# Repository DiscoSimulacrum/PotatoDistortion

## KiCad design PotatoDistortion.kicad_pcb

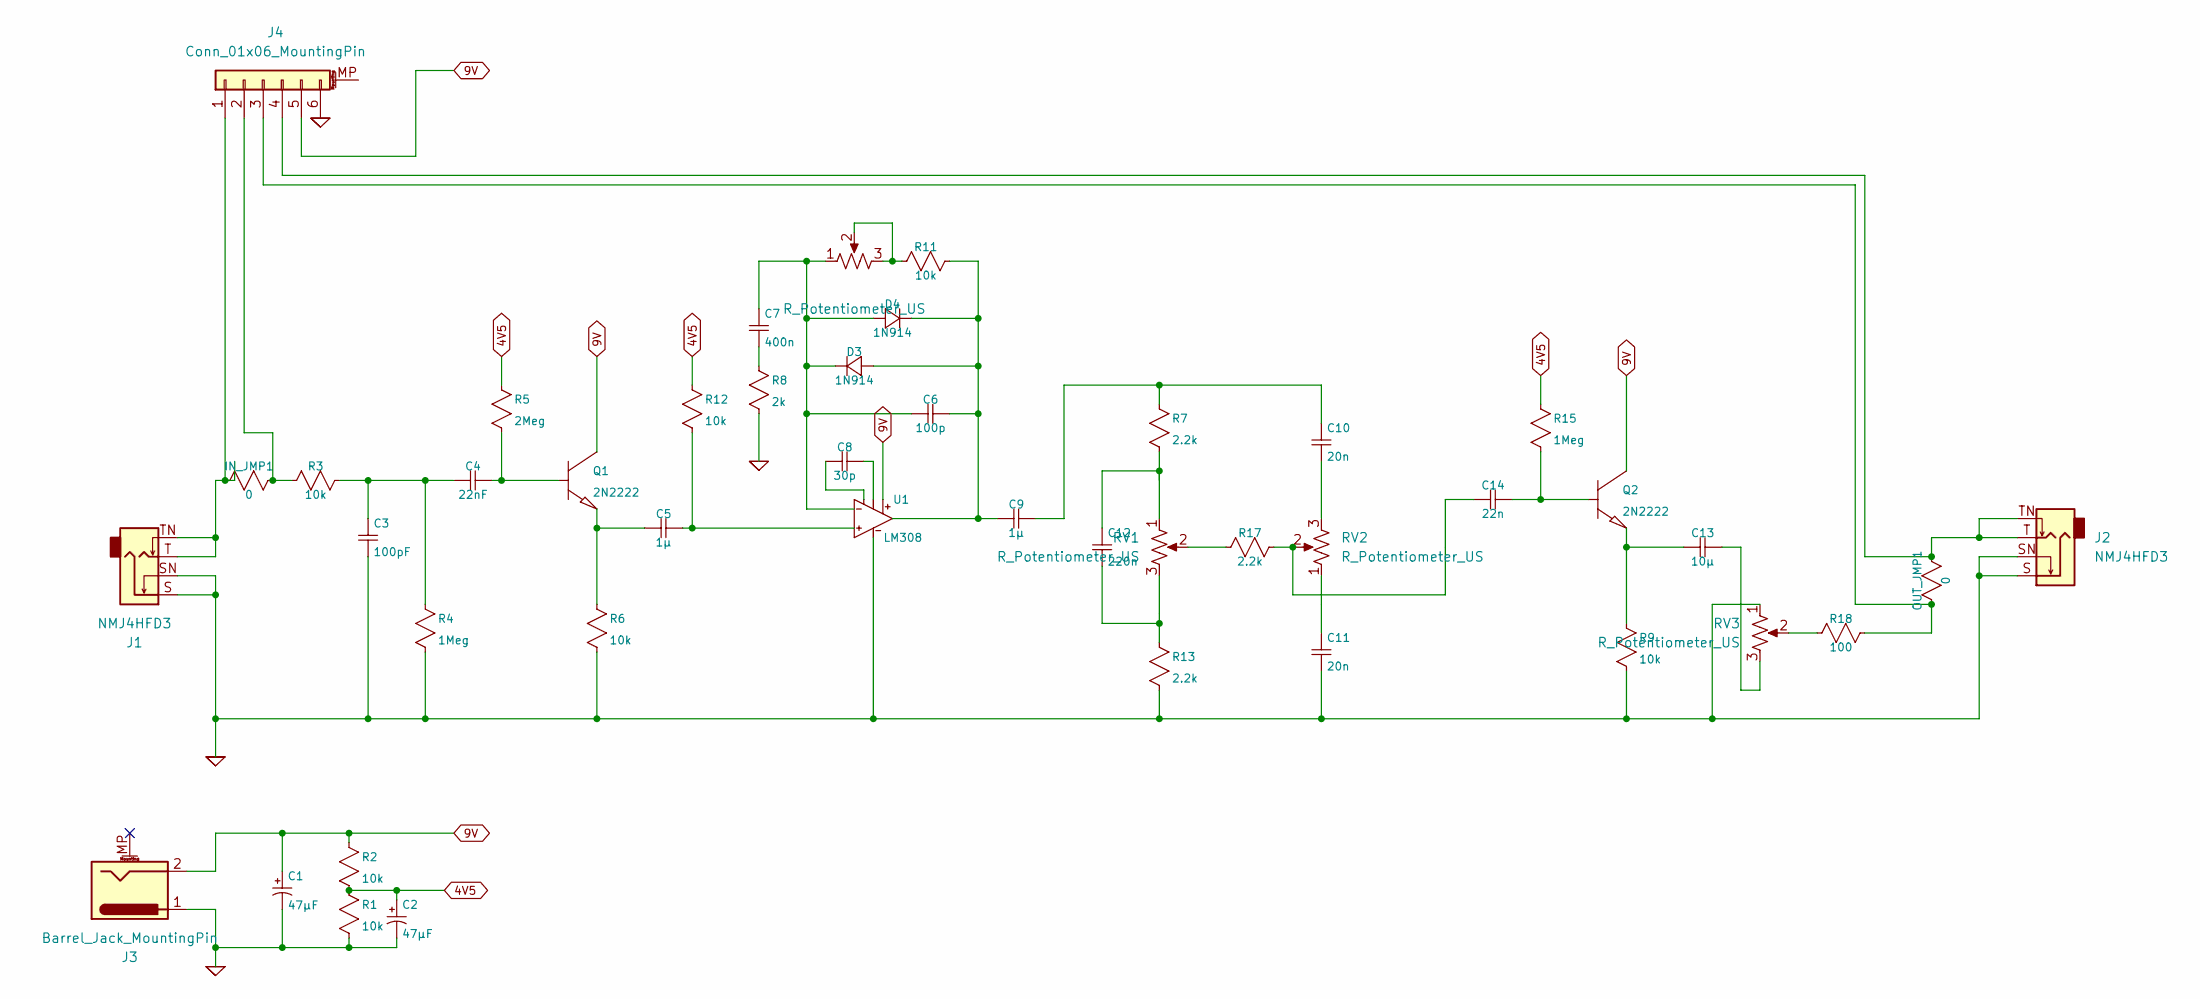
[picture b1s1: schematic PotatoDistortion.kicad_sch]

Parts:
C1, C2: 47µF; CP_Radial_D4.0mm_P2.00mm
C3: 100pF; C_Disc_D4.3mm_W1.9mm_P5.00mm
C4: 22nF; C_Disc_D4.3mm_W1.9mm_P5.00mm
C5, C9: 1µ; C_Disc_D4.3mm_W1.9mm_P5.00mm
C6: 100p; C_Disc_D4.3mm_W1.9mm_P5.00mm
C7: 400n; C_Disc_D4.3mm_W1.9mm_P5.00mm
C8: 30p; C_Disc_D4.3mm_W1.9mm_P5.00mm
C10, C11: 20n; C_Disc_D4.3mm_W1.9mm_P5.00mm
C12: 220n; C_Disc_D4.3mm_W1.9mm_P5.00mm
C13: 10µ; C_Disc_D4.3mm_W1.9mm_P5.00mm
C14: 22n; C_Disc_D4.3mm_W1.9mm_P5.00mm
D3, D4: 1N914; D_DO-201AE_P12.70mm_Horizontal
IN_JMP1: 0; R_Axial_DIN0207_L6.3mm_D2.5mm_P7.62mm_Horizontal
J1, J2: NMJ4HFD3; Jack_6.35mm_Neutrik_NMJ4HFD3_Horizontal
J3: Barrel_Jack_MountingPin; BarrelJack_Horizontal
J4: Conn_01x06_MountingPin; PinSocket_1x06_P2.00mm_Vertical
OUT_JMP1: 0; R_Axial_DIN0207_L6.3mm_D2.5mm_P7.62mm_Horizontal
Q1, Q2: 2N2222; TO-92
R1, R2, R3, R6, R9, R11, R12: 10k; R_Axial_DIN0309_L9.0mm_D3.2mm_P12.70mm_Horizontal
R4, R15: 1Meg; R_Axial_DIN0309_L9.0mm_D3.2mm_P12.70mm_Horizontal
R5: 2Meg; R_Axial_DIN0309_L9.0mm_D3.2mm_P12.70mm_Horizontal
R7, R13, R17: 2.2k; R_Axial_DIN0309_L9.0mm_D3.2mm_P12.70mm_Horizontal
R8: 2k; R_Axial_DIN0309_L9.0mm_D3.2mm_P12.70mm_Horizontal
R18: 100; R_Axial_DIN0309_L9.0mm_D3.2mm_P12.70mm_Horizontal
RV1, RV2, RV3, RV4: R_Potentiometer_US; Potentiometer_Alps_RK09L_Single_Vertical
U1: LM308; DIP-8_W7.62mm_Socket_LongPads

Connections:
0: C1.2 (B), C2.2 (B), C3.2, C11.2, J1.S, J1.SN, J2.S, J2.SN, J3.1, J4.6, R1.2, R4.2, R6.2, R8.2, R9.2, R13.2, RV3.1, U1.4 (V-)
4V5: C2.1 (A), R1.1, R2.2, R5.1, R12.1, R15.1
9V: C1.1 (A), J3.2, J4.5, Q1.1 (C), Q2.1 (C), R2.1, U1.3 (V+)
unnamed: C3.1, C4.2, R3.1, R4.1
unnamed: C7.2, R8.1
unnamed: C9.1, C10.1, R7.1
unnamed: C10.2, RV2.3
unnamed: C11.1, RV2.1
unnamed: C12.1, R7.2, RV1.1
unnamed: C12.2, R13.1, RV1.3
unnamed: C13.1, RV3.3
unnamed: C14.2, R17.1, RV2.2
unnamed: C6.1, C9.2, D3.1 (+), D4.2 (-), R11.1, U1.5 (OUT)
unnamed: C6.2, C7.1, D3.2 (-), D4.1 (+), RV4.1, U1.2 (In-)
unnamed: IN_JMP1.2, J1.T, J1.TN, J4.1
unnamed: IN_JMP1.1, J4.2, R3.2
unnamed: J4.3, OUT_JMP1.2, R18.1
unnamed: J2.T, J2.TN, J4.4, OUT_JMP1.1
unnamed: C4.1, Q1.2 (B), R5.2
unnamed: C5.2, Q1.3 (E), R6.1
unnamed: C14.1, Q2.2 (B), R15.2
unnamed: C13.2, Q2.3 (E), R9.1
unnamed: R11.2, RV4.2, RV4.3
unnamed: R17.2, RV1.2
unnamed: R18.2, RV3.2
unnamed: C8.2, U1.6 (COMP1)
unnamed: C8.1, U1.7 (COMP2)
unnamed: C5.1, R12.2, U1.1 (In+)

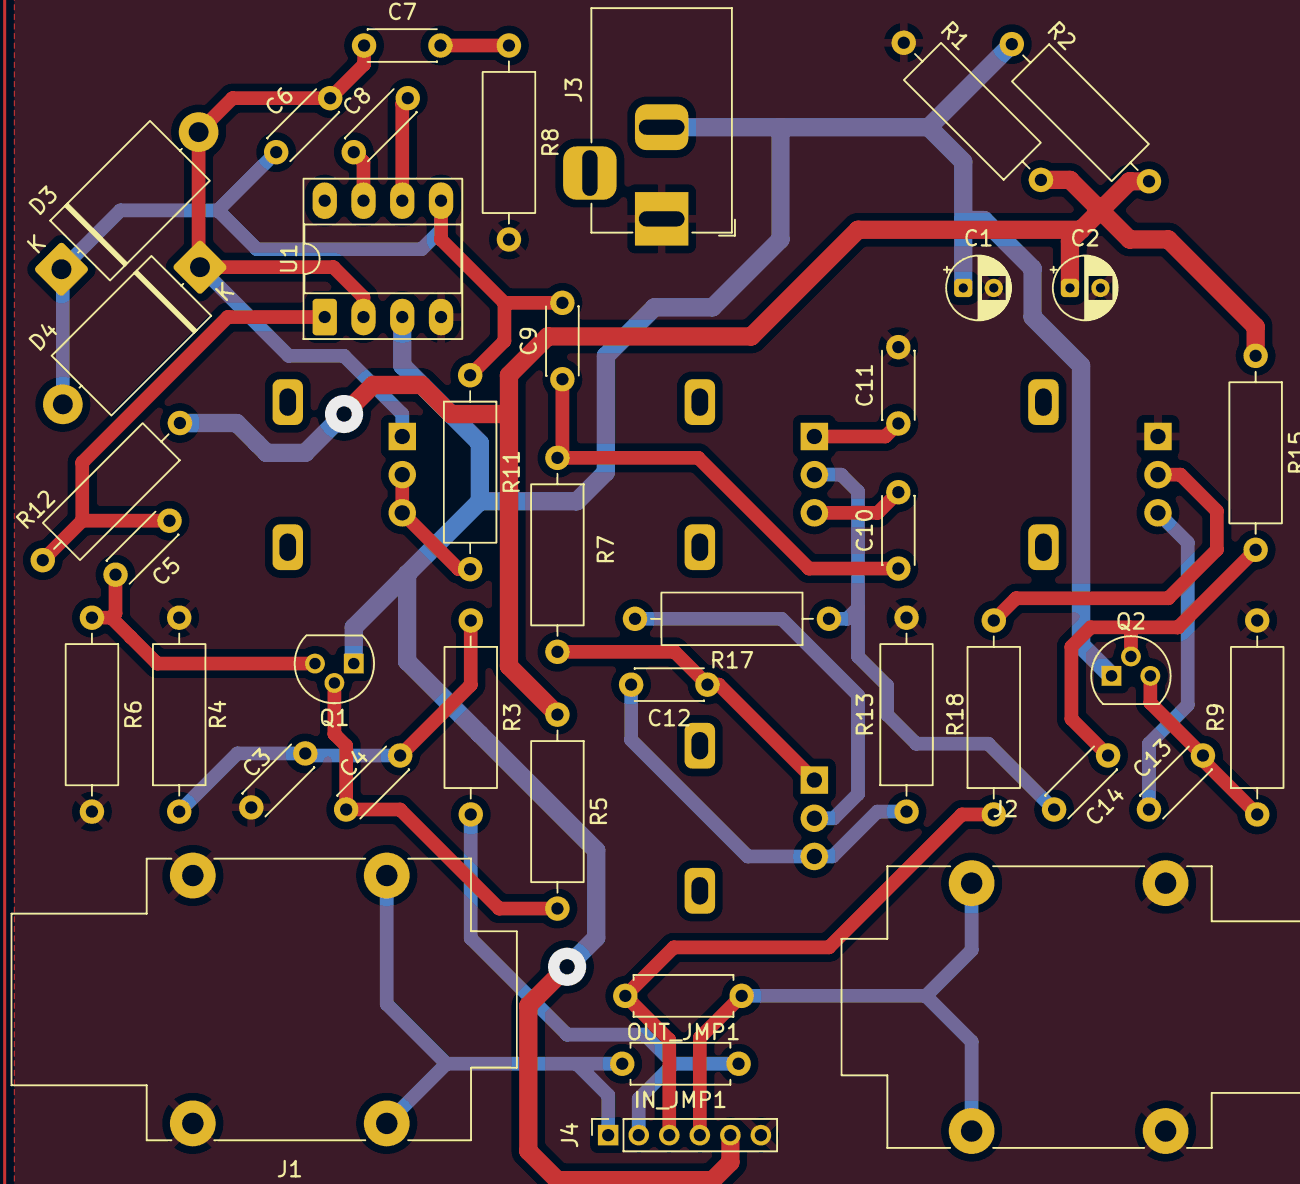
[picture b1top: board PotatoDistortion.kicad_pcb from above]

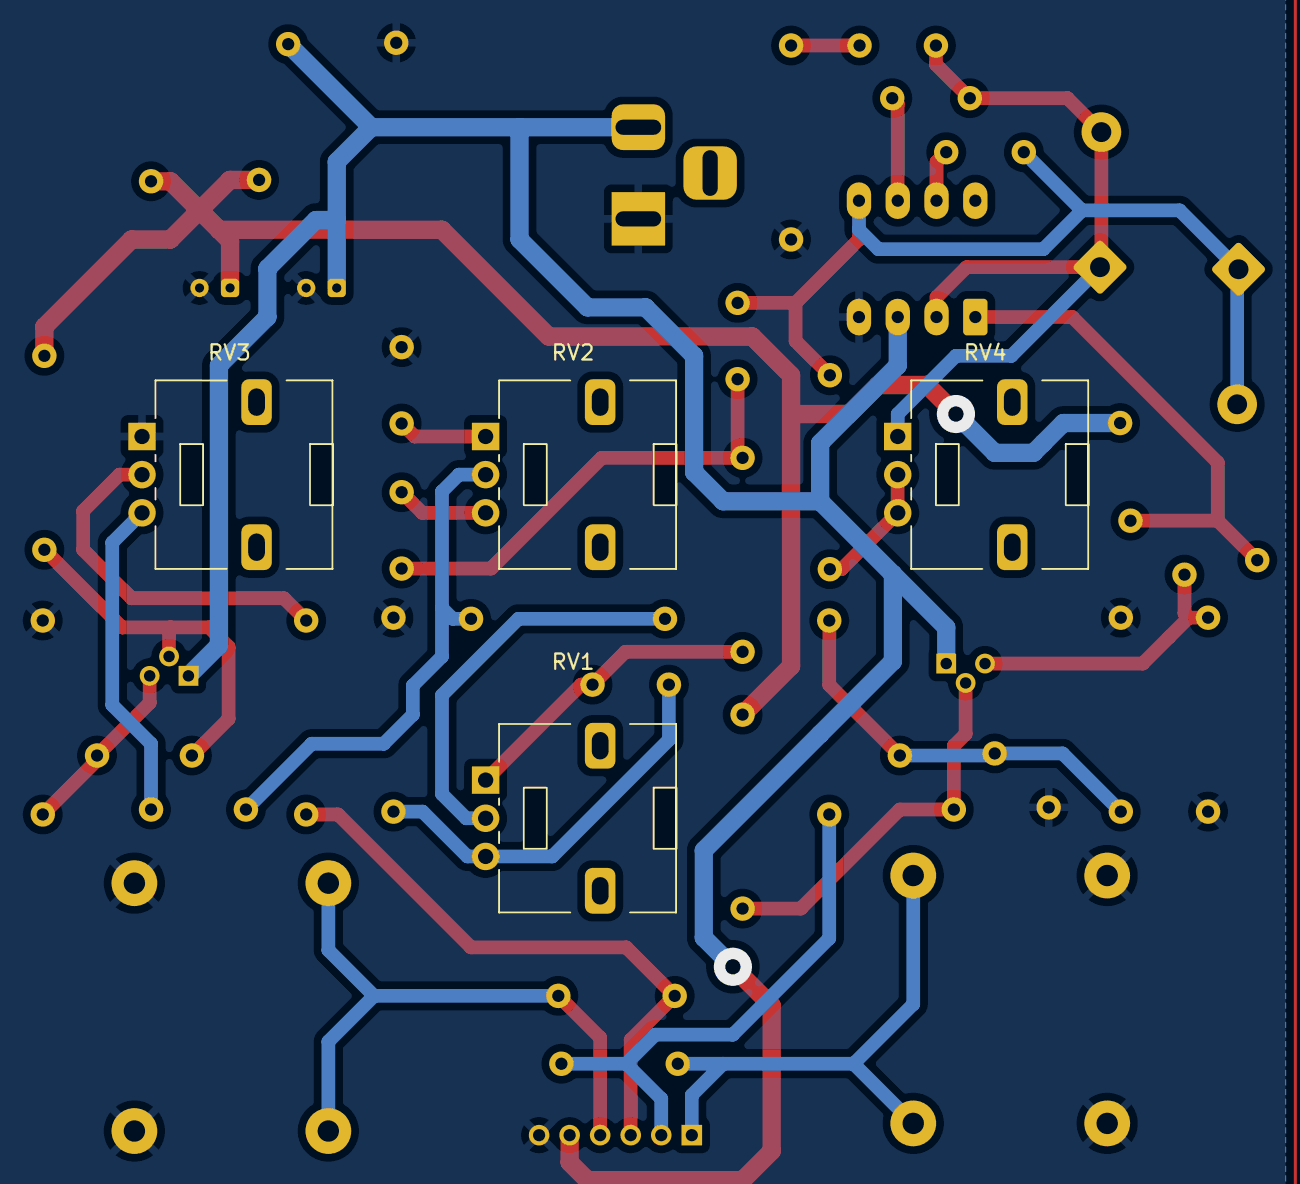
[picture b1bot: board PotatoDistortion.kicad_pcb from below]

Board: 2 copper layers, 44 parts (4 on the bottom side), 28 nets.
